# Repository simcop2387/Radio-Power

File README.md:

My new car radio draws too much standby power and eventually drains the car battery when sitting for a week or two.  This is a quick board to fix it.

It uses a P-Channel MOSFET to switch the power to the radio, so that it's only got power when the ACC power line is live, or the micro-controller (attiny85) keeps power going.

The attiny85 monitors the battery voltage and turns off the P-Channel MOSFET when the battery voltage drops below 11.75V (subject to be changed), or about 4 days has passed.

Once the P-Channel MOSFET has been turned off, it won't turn on again until the ACC line becomes live again.  This will only happen when starting the car.

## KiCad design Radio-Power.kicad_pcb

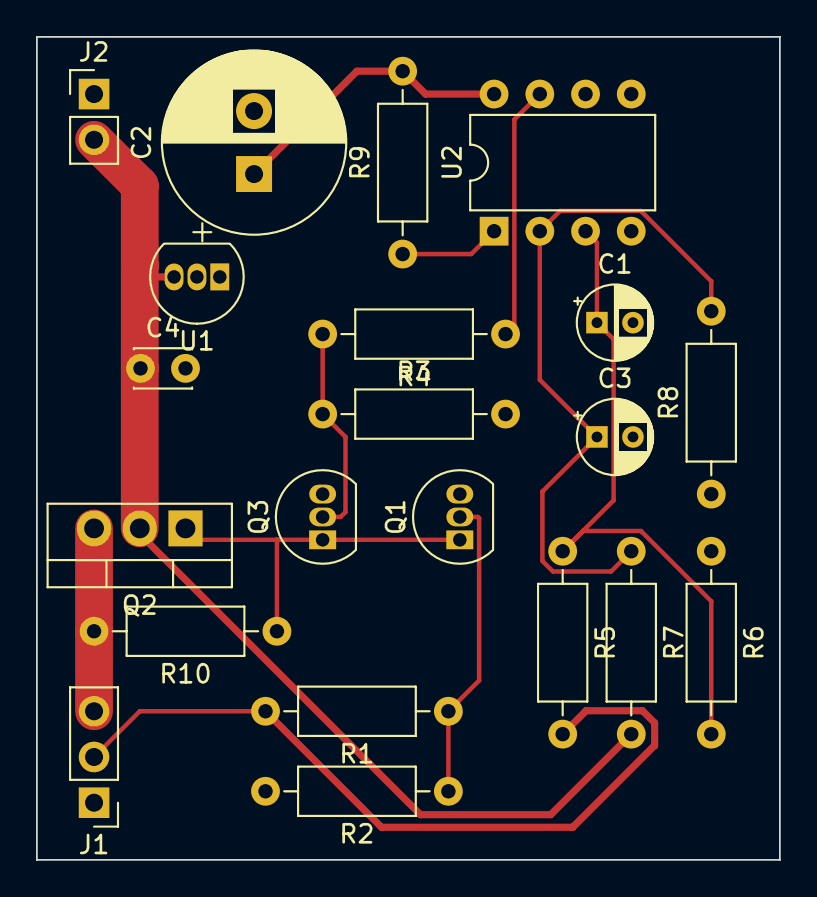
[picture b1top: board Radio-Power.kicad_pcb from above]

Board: 2 copper layers, 41.3 x 45.7 mm, 21 parts (0 on the bottom side), 12 nets.

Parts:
C1, C3: 1uF; CP_Radial_D4.0mm_P2.00mm
C2: 10uF; CP_Radial_D10.0mm_P3.50mm
C4: 100nF; C_Disc_D3.0mm_W2.0mm_P2.50mm
J1: Input; PinHeader_1x03_P2.54mm_Vertical
J2: Radio Power; PinHeader_1x02_P2.54mm_Vertical
Q1, Q3: BS170; TO-92_Inline
Q2: FQP27P06; TO-220-3_Vertical
R1, R4: 100; R_Axial_DIN0207_L6.3mm_D2.5mm_P10.16mm_Horizontal
R2, R3, R9, R10: 10K; R_Axial_DIN0207_L6.3mm_D2.5mm_P10.16mm_Horizontal
R5, R7: 47K; R_Axial_DIN0207_L6.3mm_D2.5mm_P10.16mm_Horizontal
R6, R8: 15K; R_Axial_DIN0207_L6.3mm_D2.5mm_P10.16mm_Horizontal
U1: LM2936-5.0_TO92; TO-92_Inline
U2: ATtiny85-20PU; DIP-8_W7.62mm

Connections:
5V: C2.1, R9.2, U1.1, U2.8
ACC: J1.2, R1.2, R5.2
Bat+: J1.3, Q2.3, R10.2
GND: C1.2, C2.2, C3.2, C4.2, J1.1, J2.1, Q1.3, Q3.3, R2.2, R3.2, R6.1, R8.1, U1.2, U2.4
unnamed: C1.1, R5.1, R6.2, U2.3
unnamed: C3.1, R7.1, R8.2, U2.2
unnamed: Q1.1, Q2.1, Q3.1, R10.1
unnamed: Q1.2, R1.1, R2.1
unnamed: Q3.2, R3.1, R4.2
unnamed: R4.1, U2.7
unnamed: R9.1, U2.1
Switched: C4.1, J2.2, Q2.2, R7.2, U1.3

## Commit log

2020-04-24 Mostly ready, need proper footprint for in/out terminal blocks
2020-04-24 Add readme
2020-04-24 Try to add schematic to page
2020-04-24 Make png
2020-04-24 Update readme with png
2020-04-24 Forgot a resistor
2020-04-24 Fix rendered schematic
2020-04-24 Gerbers and some minor changes
2020-04-25 Change some things, use switched power for measurement to prevent accidental power flow into the uC
2020-04-25 Replot everything
2020-04-25 Board updated, switched to lm2936 for 5v regulator
2020-04-25 Update readme to include board look
2020-04-25 Minor updates, add a cap and move the regulator
